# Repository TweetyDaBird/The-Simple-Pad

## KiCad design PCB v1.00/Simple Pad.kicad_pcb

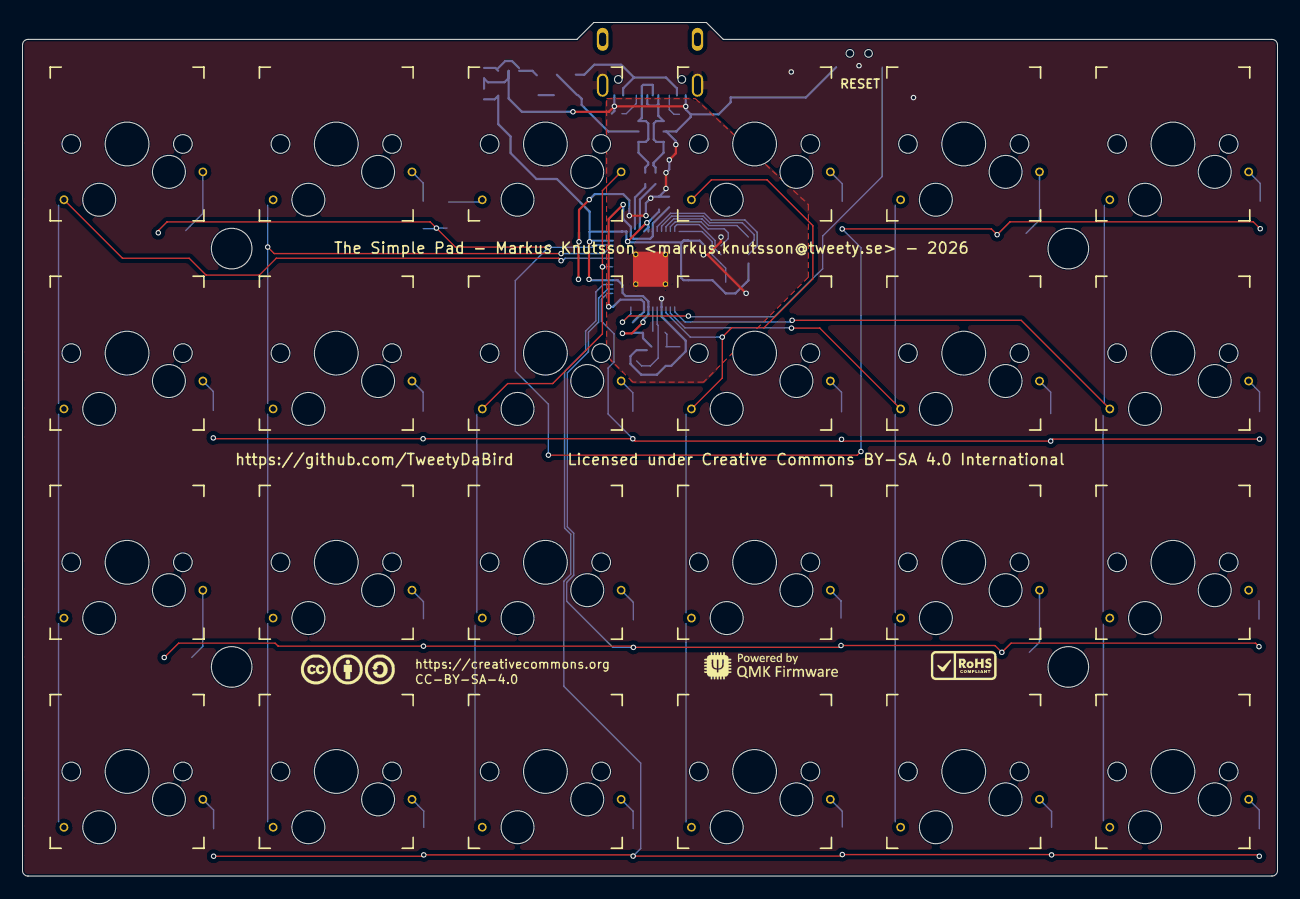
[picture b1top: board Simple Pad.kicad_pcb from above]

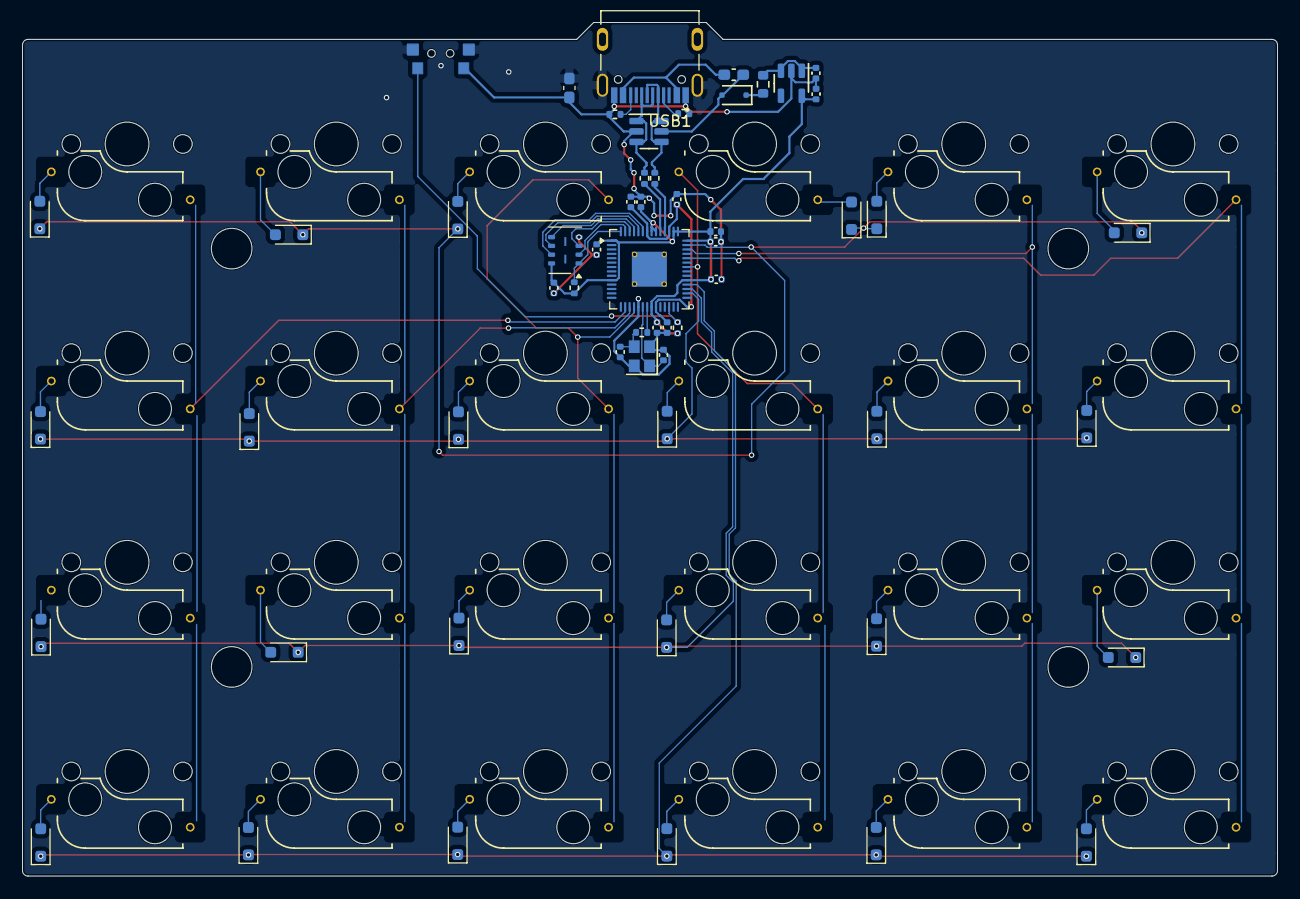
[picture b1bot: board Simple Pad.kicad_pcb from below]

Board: 2 copper layers, 114.3 x 77.7 mm, 87 parts (56 on the bottom side), 58 nets.

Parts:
C7, C13, C16, C17: 1uF; C_0402_1005Metric
C8, C9, C10, C11, C12, C14, C15, C18: 100nF; C_0402_1005Metric
C19, C20: 30pF; C_0402_1005Metric
D1, D2, D3, D4, D5, D6, D8, D9, D10, D11, D12, D13, D15, D16, D17, D18, D19, D20, D22, D23, D24, D25, D26, D27: 1N4148W; D_SOD-323_HandSoldering
F1: CF06V5TR50; R_0603_1608Metric
FB4, FB5: BLM18SG700TZ1D; C_0603_1608Metric_Pad1.08x0.95mm_HandSolder
H1, H2, H3, H4: Spacer_PCB; Spacer PCB hole
Logo1: RoHS_Logo; RoHs
Logo3: CC-BY-SA-4.0; CC_BY_SA_40_line
Logo4: QMK_Logo; Powered_by_QMK
R7, R8: 5.1K; R_0402_1005Metric
R13, R18: 10K; R_0402_1005Metric
R15: 1K; R_0402_1005Metric
R16, R17: 27R; R_0402_1005Metric
RES1: YTS-A002
SW1, SW2, SW3, SW4, SW5, SW6, SW8, SW9, SW10, SW11, SW12, SW13, SW15, SW16, SW17, SW18, SW19, SW20, SW22, SW23, SW24, SW25, SW26, SW27: SW_Push; SW_MX_HotSwap_via
U5: SPX3819M5-L-3-3/TR; SOT-23-5
U6: SRV05-4; SOT-23-6
U7: W25Q32JVUUIQ; USON-8_4x3mm_P0.8mm
U8: RP2040; QFN-56-1EP_7x7mm_P0.4mm_EP3.2x3.2mm_ThermalVias
USB1: USB_C_Receptacle_USB2.0; HRO_TYPE-C-31-M-12
Y1: TXM12M0004252LBCEO00T; Crystal_SMD_2520-4Pin_2.5x2.0mm
ZD1: 1N5819WS; D_SOD-323F

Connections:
+1V1: C13.1, C14.1, C15.1, U8.23 (DVDD), U8.45 (VREG_VOUT), U8.50 (DVDD)
+3V3: C7.1, C8.1, C9.1, C10.1, C11.1, C12.1, C17.1, C18.1, R13.1, R18.1, U5.5 (OUT), U7.8 (VCC), U8.1 (IOVDD), U8.10 (IOVDD), U8.22 (IOVDD), U8.33 (IOVDD), U8.42 (IOVDD), U8.43 (ADC_AVDD), U8.44 (VREG_IN), U8.48 (USB_VDD), U8.49 (IOVDD)
+5V: C16.1, F1.2, U5.1 (IN), U5.3 (EN)
/DN: R17.1, U8.46 (USB_DM)
/DP: R16.1, U8.47 (USB_DP)
Col0: SW1.2, SW8.2, SW15.2, SW22.2, U8.38 (GPIO26_ADC0)
Col1: SW2.2, SW9.2, SW16.2, SW23.2, U8.40 (GPIO28_ADC2)
Col2: SW3.1, SW10.2, SW17.2, SW24.2, U8.36 (GPIO24)
Col3: SW4.2, SW11.2, SW18.2, SW25.2, U8.18 (GPIO15)
Col4: SW5.2, SW12.2, SW19.2, SW26.2, U8.17 (GPIO14)
Col5: SW6.2, SW13.2, SW20.2, SW27.2, U8.16 (GPIO13)
D+: R16.2, U6.1 (IO1), U6.3 (IO2), USB1.A6 (D+), USB1.B6 (D+)
D-: R17.2, U6.4 (IO3), U6.6 (IO4), USB1.A7 (D-), USB1.B7 (D-)
Earth_Protective: FB5.1, RES1.3, USB1.S1 (SHIELD)
GND: C7.2, C8.2, C9.2, C10.2, C11.2, C12.2, C13.2, C14.2, C15.2, C16.2, C17.2, C18.2, C19.2, C20.2, FB5.2, R7.1, R8.2, RES1.2, U5.2 (GND), U6.2 (VN), U7.4 (GND), U8.19 (TESTEN), U8.57 (GND), USB1.A1 (GND), USB1.A12 (GND), USB1.B1 (GND), USB1.B12 (GND), Y1.2, Y1.4
unnamed: C20.1, R15.2, Y1.3
unnamed: D1.2 (A), SW1.1
unnamed: D2.2 (A), SW2.1
unnamed: D3.2 (A), SW3.2
unnamed: D4.2 (A), SW4.1
unnamed: D5.2 (A), SW5.1
unnamed: D6.2 (A), SW6.1
unnamed: D8.2 (A), SW8.1
unnamed: D9.2 (A), SW9.1
unnamed: D10.2 (A), SW10.1
unnamed: D11.2 (A), SW11.1
unnamed: D12.2 (A), SW12.1
unnamed: D13.2 (A), SW13.1
unnamed: D15.2 (A), SW15.1
unnamed: D16.2 (A), SW16.1
unnamed: D17.2 (A), SW17.1
unnamed: D18.2 (A), SW18.1
unnamed: D19.2 (A), SW19.1
unnamed: D20.2 (A), SW20.1
unnamed: D22.2 (A), SW22.1
unnamed: D23.2 (A), SW23.1
unnamed: D24.2 (A), SW24.1
unnamed: D25.2 (A), SW25.1
unnamed: D26.2 (A), SW26.1
unnamed: D27.2 (A), SW27.1
unnamed: FB4.1, USB1.A4 (VBUS), USB1.A9 (VBUS), USB1.B4 (VBUS), USB1.B9 (VBUS)
unnamed: U7.6 (CLK), U8.52 (QSPI_SCLK)
unnamed: U7.5 (DI(IO0)), U8.53 (QSPI_SD0)
unnamed: U7.2 (DO(IO1)), U8.55 (QSPI_SD1)
unnamed: U7.3 (IO2), U8.54 (QSPI_SD2)
unnamed: U7.7 (IO3), U8.51 (QSPI_SD3)
unnamed: R13.2, U7.1 (~CS), U8.56 (QSPI_SS)
unnamed: R18.2, RES1.1, U8.26 (RUN)
unnamed: C19.1, U8.20 (XIN), Y1.1
unnamed: R15.1, U8.21 (XOUT)
unnamed: R7.2, USB1.A5 (CC1)
unnamed: R8.1, USB1.B5 (CC2)
unnamed: F1.1, ZD1.1 (K)
Row0: D1.1 (K), D2.1 (K), D3.1 (K), D4.1 (K), D5.1 (K), D6.1 (K), U8.41 (GPIO29_ADC3)
Row1: D8.1 (K), D9.1 (K), D10.1 (K), D11.1 (K), D12.1 (K), D13.1 (K), U8.30 (GPIO19)
Row2: D15.1 (K), D16.1 (K), D17.1 (K), D18.1 (K), D19.1 (K), D20.1 (K), U8.31 (GPIO20)
Row3: D22.1 (K), D23.1 (K), D24.1 (K), D25.1 (K), D26.1 (K), D27.1 (K), U8.32 (GPIO21)
VBUS: FB4.2, U6.5 (VP), ZD1.2 (A)

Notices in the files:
PCB v1.00/Simple Pad.kicad_pcb:
Licensed under Creative Commons BY-SA 4.0 International
